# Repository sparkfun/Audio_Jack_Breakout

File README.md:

SparkFun Audio Jack Breakout
========================================

[*SparkFun Audio Jack Breakout (PRT-10588)*](https://www.sparkfun.com/products/10588)

Simple breakout board for the 3.5mm audio jack. 
Use this breakout (shipped bare) to allow breadboard or SIP access to the super-common 3.5mm audio jack. 
All five pins are broken out.

Repository Contents
-------------------

* **/Hardware** - Eagle design files (.brd, .sch)

Documentation
--------------
* **[SparkFun Fritzing repo](https://github.com/sparkfun/Fritzing_Parts)** - Fritzing diagrams for SparkFun products.
* **[SparkFun 3D Model repo](https://github.com/sparkfun/3D_Models)** - 3D models of SparkFun products. 

License Information
-------------------
This product is _**open source**_! 

The **hardware** is released under [Creative Commons ShareAlike 4.0 International](https://creativecommons.org/licenses/by-sa/4.0/).

Please use, reuse, and modify these files as you see fit. Please maintain attribution to SparkFun Electronics and release anything derivative under the same license.

Distributed as-is; no warranty is given.

- Your friends at SparkFun.

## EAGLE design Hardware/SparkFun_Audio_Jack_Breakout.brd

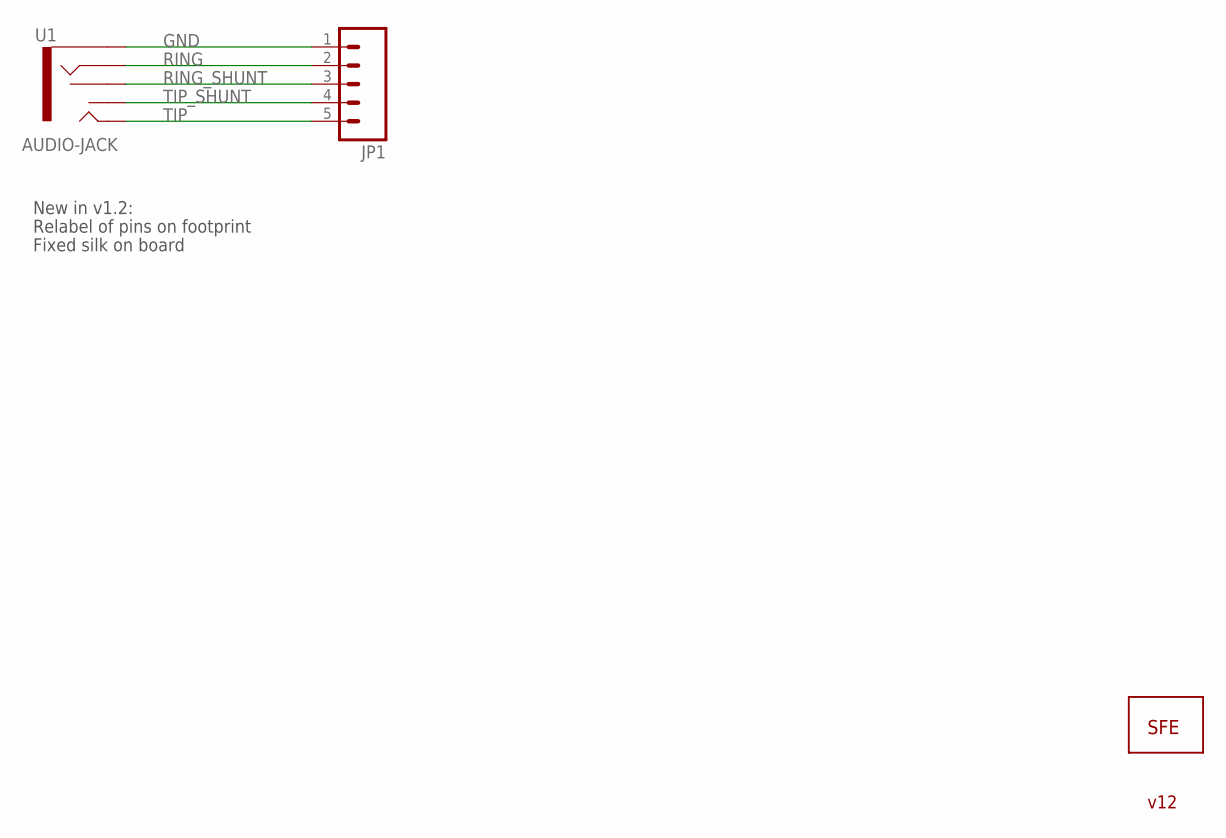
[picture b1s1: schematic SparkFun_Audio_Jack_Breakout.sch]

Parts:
JP1: M05PTH; 1X05
U1: AUDIO-JACK
U$1: LOGO-SFESK; SFE-LOGO-FLAME

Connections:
GND: JP1.1, U1.SLEEVE
RING: JP1.2, U1.RING
RING_SHUNT: JP1.3, U1.RSH
TIP: JP1.5, U1.TIP
TIP_SHUNT: JP1.4, U1.TSH

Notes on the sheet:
Relabel of pins on footprint
New in v1.2:
Fixed silk on board
v12

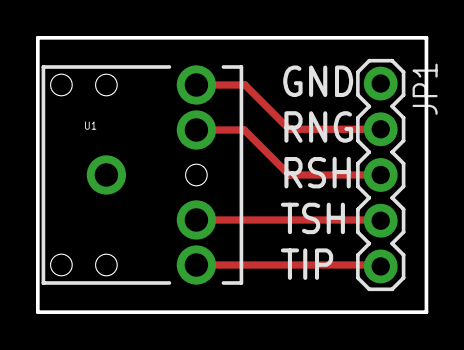
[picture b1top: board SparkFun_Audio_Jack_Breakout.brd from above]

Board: 2 copper layers, 21.6 x 15.2 mm, 3 parts (1 on the bottom side), 5 nets.

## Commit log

2015-05-01 Initial hardware files addition, updating README
